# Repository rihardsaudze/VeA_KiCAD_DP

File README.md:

# VeA_KiCAD_R4

**ENG:** This is the main repository for my course work project in PCB design.  
Main objective of this course work is to create an Arduino Uno R3 clone/version, that is adjusted and modified for my own needs.

**LAT:** Šī ir mana projekta galvenā repozitorija, kurā tiks veidots kursa darbs "Datorizētā iespiedplašu projektēšanā"  
Kursa darba laikā plānots izveidot Arduino Uno R3 klonu/versiju, pielāgotu un pārveidotu savām vajadzībām.

***Author/Autors:*** *Rihards*

**Progress:**  
-15.05.2020 pabeigta principiālā shēma (finished schematic)  
-27.05.2020 pabeigts PCB dizains (finished PCB design)  
-09.06.2020 izveidoti GERBER un drill faili (generated GBR and DRL files)

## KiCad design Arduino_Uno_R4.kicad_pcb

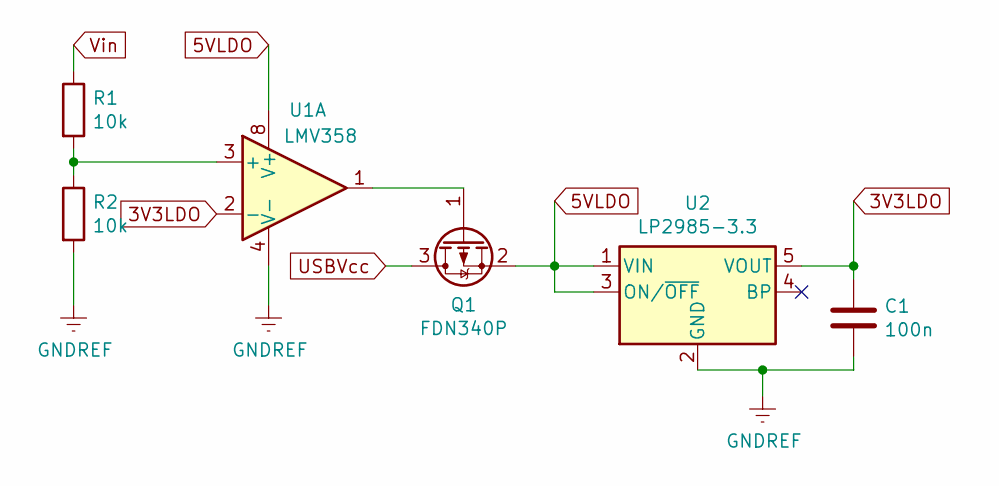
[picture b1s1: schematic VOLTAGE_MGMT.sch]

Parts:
C1: 100n; C_0603_1608Metric
Q1: FDN340P; SOT-23
R1, R2: 10k; R_0603_1608Metric
U1: LMV358; MSOP-8_3x3mm_P0.65mm
U2: LP2985-3.3; SOT-23-5

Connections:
3V3LDO: C1.1, U1.2 (-), U2.5 (VOUT); also elsewhere on the board
5VLDO: Q1.2 (S), U1.8 (V+), U2.1 (VIN), U2.3 (ON/~OFF~); also elsewhere on the board
unnamed: Q1.1 (G), U1.1
unnamed: R1.2, R2.1, U1.3 (+)
USBVcc: Q1.3 (D); also elsewhere on the board
USB_GND: C1.2, R2.2, U1.4 (V-), U2.2 (GND); also elsewhere on the board
Vin: R1.1; also elsewhere on the board

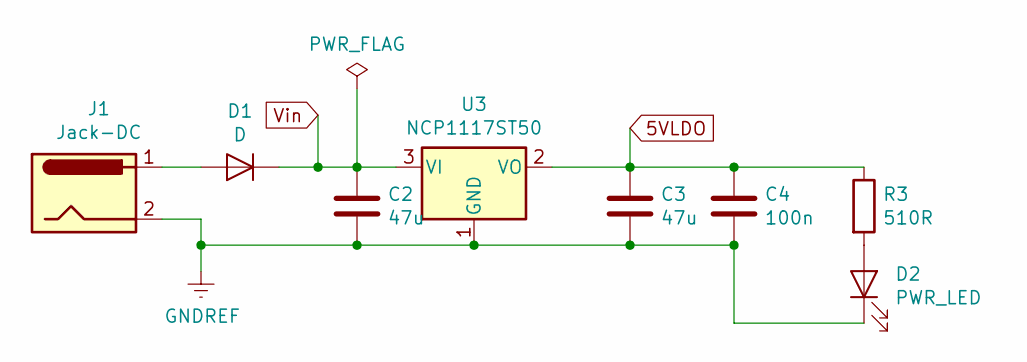
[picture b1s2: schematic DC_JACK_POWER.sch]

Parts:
C2, C3: 47u; C_0805_2012Metric
C4: 100n; C_0603_1608Metric
D1: D; D_SMF
D2: PWR_LED; LED_0603_1608Metric
J1: Jack-DC; DC_Jack
R3: 510R; R_0603_1608Metric
U3: NCP1117ST50; SOT-223-3_TabPin2

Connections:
5VLDO: C3.1, C4.1, R3.1, U3.2 (VO); also elsewhere on the board
unnamed: D1.2 (A), J1.1
unnamed: D2.2 (A), R3.2
USB_GND: C2.2, C3.2, C4.2, D2.1 (K), J1.2, U3.1 (GND); also elsewhere on the board
Vin: C2.1, D1.1 (K), U3.3 (VI); also elsewhere on the board

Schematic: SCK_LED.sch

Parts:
D3: SCK_LED; LED_0603_1608Metric
R4: 510R; R_0603_1608Metric
U1, U4: LMV358; MSOP-8_3x3mm_P0.65mm

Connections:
ICSP_SCK: U1.5 (+); also elsewhere on the board
unnamed: D3.2 (A), R4.2
unnamed: R4.1, U1.6 (-), U1.7
USB_GND: D3.1 (K), U4.4 (V-); also elsewhere on the board

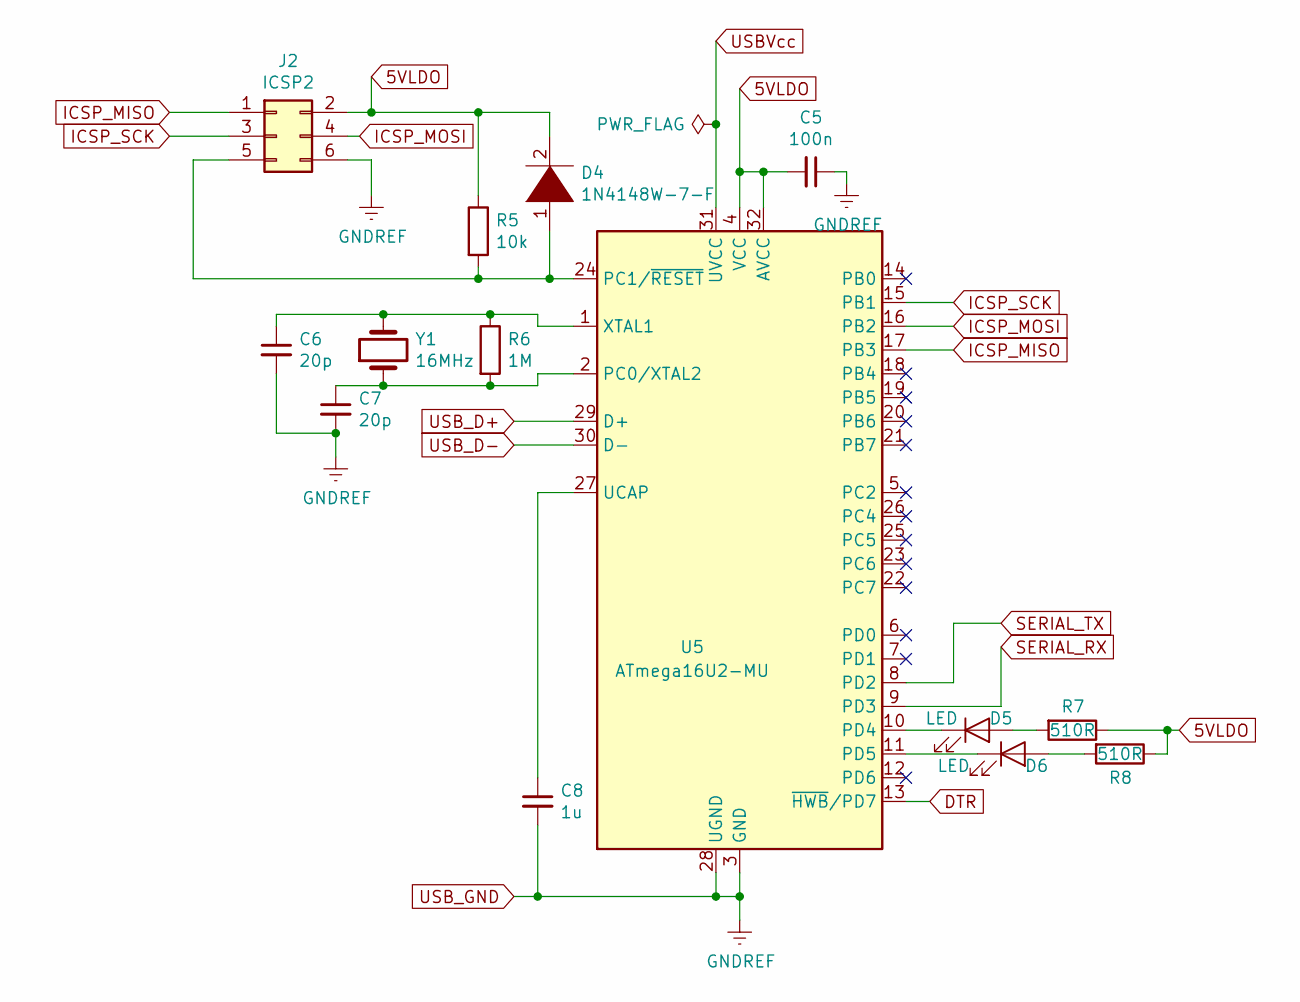
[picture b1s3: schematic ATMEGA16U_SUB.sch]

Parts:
C5: 100n; C_0603_1608Metric
C6, C7: 20p; C_0603_1608Metric
C8: 1u; C_0603_1608Metric
D4: 1N4148W-7-F; D_SOD-123
D5, D6: LED; D_0603_1608Metric
J2: ICSP2; PinHeader_2x03_P2.54mm_Vertical
R5: 10k; R_0603_1608Metric
R6: 1M; R_0603_1608Metric
R7, R8: 510R; R_0603_1608Metric
U5: ATmega16U2-MU; QFN-32-1EP_5x5mm_P0.5mm_EP3.1x3.1mm
Y1: 16MHz; HC-49S

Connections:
5VLDO: C5.2, D4.2 (A), J2.2, R5.1, R7.1, R8.1, U5.4 (VCC), U5.32 (AVCC); also elsewhere on the board
DTR: U5.13 (~HWB~/PD7); also elsewhere on the board
ICSP_MISO: J2.1, U5.17 (PB3)
ICSP_MOSI: J2.4, U5.16 (PB2)
ICSP_SCK: J2.3, U5.15 (PB1); also elsewhere on the board
unnamed: C6.1, R6.1, U5.1 (XTAL1), Y1.2
unnamed: C7.1, R6.2, U5.2 (PC0/XTAL2), Y1.1
unnamed: C8.1, U5.27 (UCAP)
unnamed: D4.1 (K), J2.5, R5.2, U5.24 (PC1/~RESET)
unnamed: D5.1 (K), U5.10 (PD4)
unnamed: D5.2 (A), R7.2
unnamed: D6.1 (K), U5.11 (PD5)
unnamed: D6.2 (A), R8.2
SERIAL_RX: U5.9 (PD3); also elsewhere on the board
SERIAL_TX: U5.8 (PD2); also elsewhere on the board
USBVcc: U5.31 (UVCC); also elsewhere on the board
USB_D+: U5.29 (D+); also elsewhere on the board
USB_D-: U5.30 (D-); also elsewhere on the board
USB_GND: C5.1, C6.2, C7.2, C8.2, J2.6, U5.3 (GND), U5.28 (UGND), U5.33 (GND); also elsewhere on the board

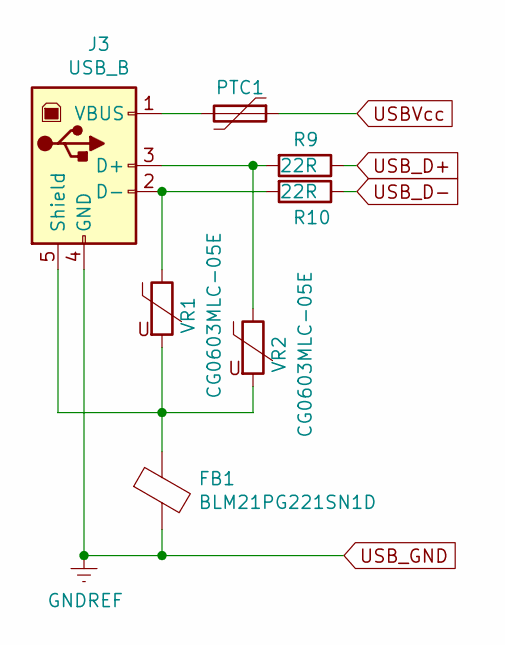
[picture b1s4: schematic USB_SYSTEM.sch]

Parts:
FB1: BLM21PG221SN1D; C_0805_2012Metric
J3: USB_B; USB_B_OST_USB-B1HSxx_Horizontal
PTC1: MF-MSMF-050-2; Fuse_1812_4532Metric
R9, R10: 22R; R_0603_1608Metric
VR1, VR2: CG0603MLC-05E; C_0603_1608Metric

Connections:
unnamed: FB1.1, J3.5 (Shield), VR1.2, VR2.2
unnamed: J3.1 (VBUS), PTC1.2
unnamed: J3.2 (D-), R10.2, VR1.1
unnamed: J3.3 (D+), R9.2, VR2.1
USBVcc: PTC1.1; also elsewhere on the board
USB_D+: R9.1; also elsewhere on the board
USB_D-: R10.1; also elsewhere on the board
USB_GND: FB1.2, J3.4 (GND); also elsewhere on the board

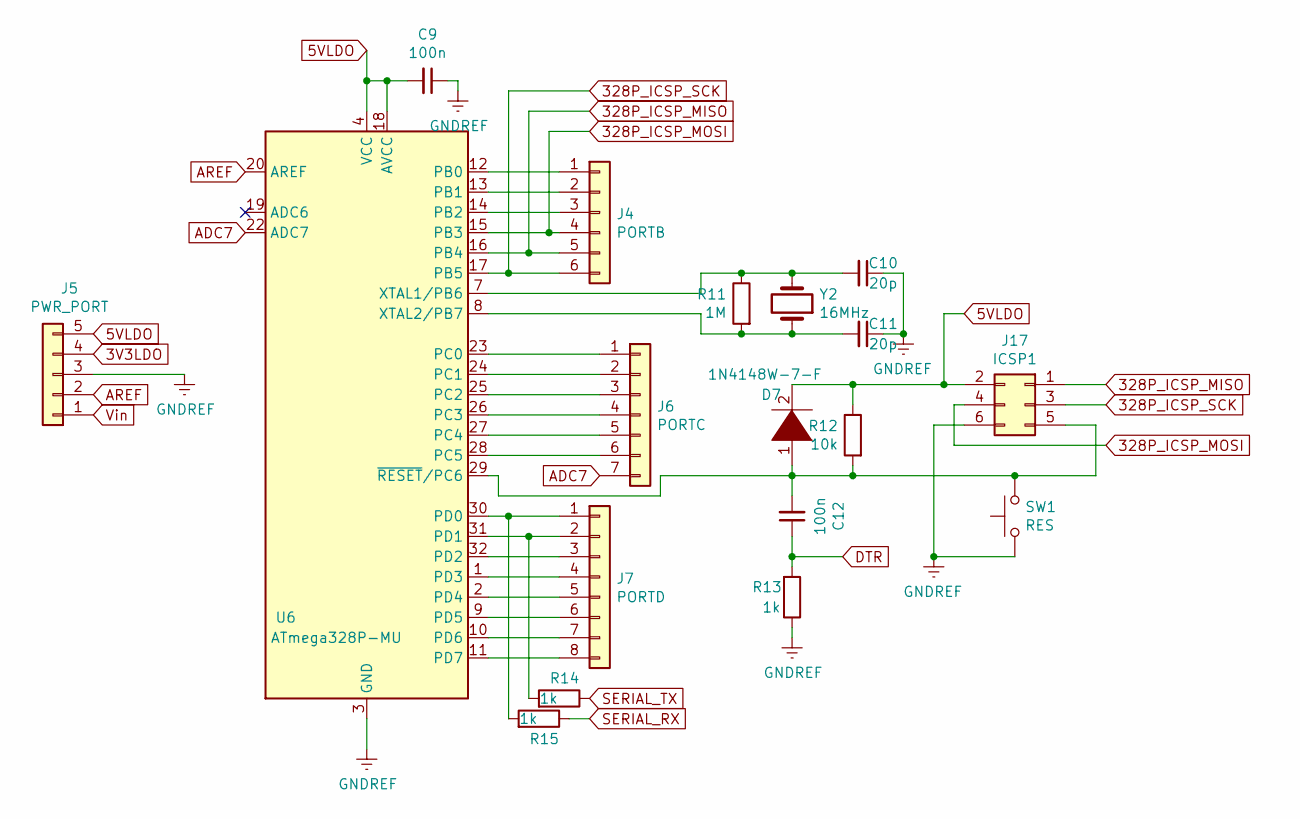
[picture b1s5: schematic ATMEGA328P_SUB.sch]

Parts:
C9, C12: 100n; C_0603_1608Metric
C10, C11: 20p; C_0603_1608Metric
D7: 1N4148W-7-F; D_SOD-123
J4: PORTB; PinHeader_1x06_P2.54mm_Vertical
J5: PWR_PORT; PinHeader_1x05_P2.54mm_Vertical
J6: PORTC; PinHeader_1x07_P2.54mm_Vertical
J7: PORTD; PinHeader_1x08_P2.54mm_Vertical
J17: ICSP1; PinHeader_2x03_P2.54mm_Vertical
R11: 1M; R_0603_1608Metric
R12: 10k; R_0603_1608Metric
R13, R14, R15: 1k; R_0603_1608Metric
SW1: RES; SW_SPST_EVQP2
U6: ATmega328P-MU; QFN-32-1EP_5x5mm_P0.5mm_EP3.1x3.1mm
Y2: 16MHz; HC-49S

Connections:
3V3LDO: J5.4; also elsewhere on the board
5VLDO: C9.2, D7.2 (A), J5.5, J17.2, R12.1, U6.4 (VCC), U6.6 (VCC), U6.18 (AVCC); also elsewhere on the board
328P_ICSP_MISO: J4.5, J17.1, U6.16 (PB4)
328P_ICSP_MOSI: J4.4, J17.4, U6.15 (PB3)
328P_ICSP_SCK: J4.6, J17.3, U6.17 (PB5)
ADC7: J6.7, U6.22 (ADC7)
AREF: J5.2, U6.20 (AREF)
DTR: C12.1, R13.2; also elsewhere on the board
unnamed: C10.2, R11.1, U6.7 (XTAL1/PB6), Y2.2
unnamed: C11.2, R11.2, U6.8 (XTAL2/PB7), Y2.1
unnamed: C12.2, D7.1 (K), J17.5, R12.2, SW1.2, U6.29 (~RESET~/PC6)
unnamed: J4.1, U6.12 (PB0)
unnamed: J4.2, U6.13 (PB1)
unnamed: J4.3, U6.14 (PB2)
unnamed: J6.1, U6.23 (PC0)
unnamed: J6.2, U6.24 (PC1)
unnamed: J6.3, U6.25 (PC2)
unnamed: J6.4, U6.26 (PC3)
unnamed: J6.5, U6.27 (PC4)
unnamed: J6.6, U6.28 (PC5)
unnamed: J7.1, R15.2, U6.30 (PD0)
unnamed: J7.2, R14.2, U6.31 (PD1)
unnamed: J7.3, U6.32 (PD2)
unnamed: J7.4, U6.1 (PD3)
unnamed: J7.5, U6.2 (PD4)
unnamed: J7.6, U6.9 (PD5)
unnamed: J7.7, U6.10 (PD6)
unnamed: J7.8, U6.11 (PD7)
SERIAL_RX: R15.1; also elsewhere on the board
SERIAL_TX: R14.1; also elsewhere on the board
USB_GND: C9.1, C10.1, C11.1, J5.3, J17.6, R13.1, SW1.1, U6.3 (GND), U6.5 (GND), U6.21 (GND), U6.33 (GND); also elsewhere on the board
Vin: J5.1; also elsewhere on the board

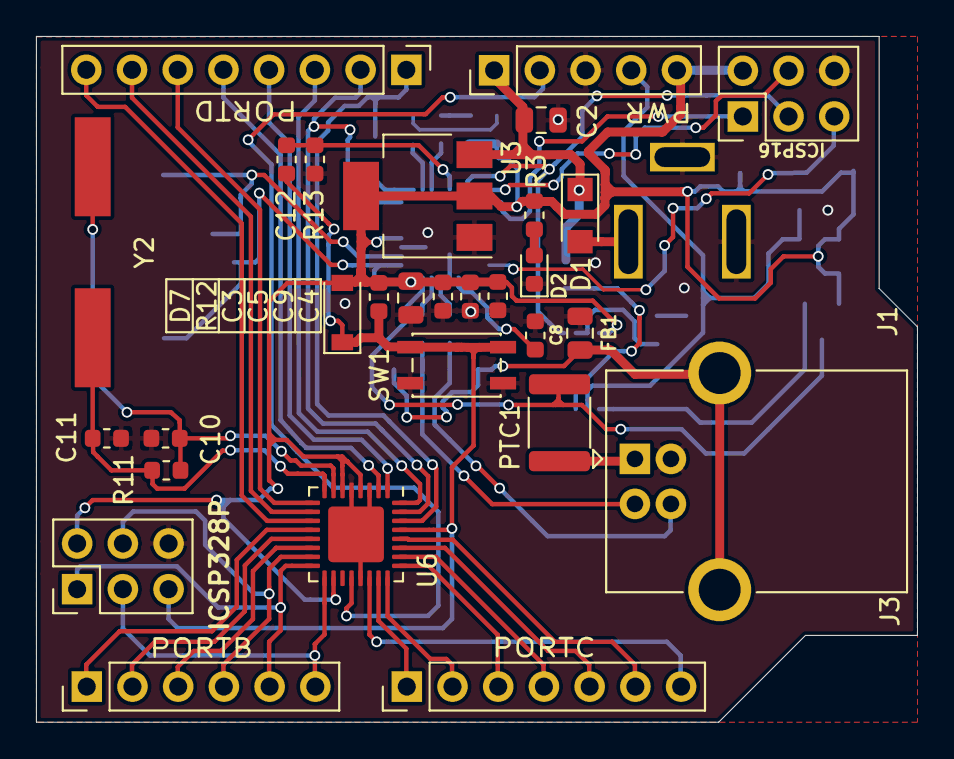
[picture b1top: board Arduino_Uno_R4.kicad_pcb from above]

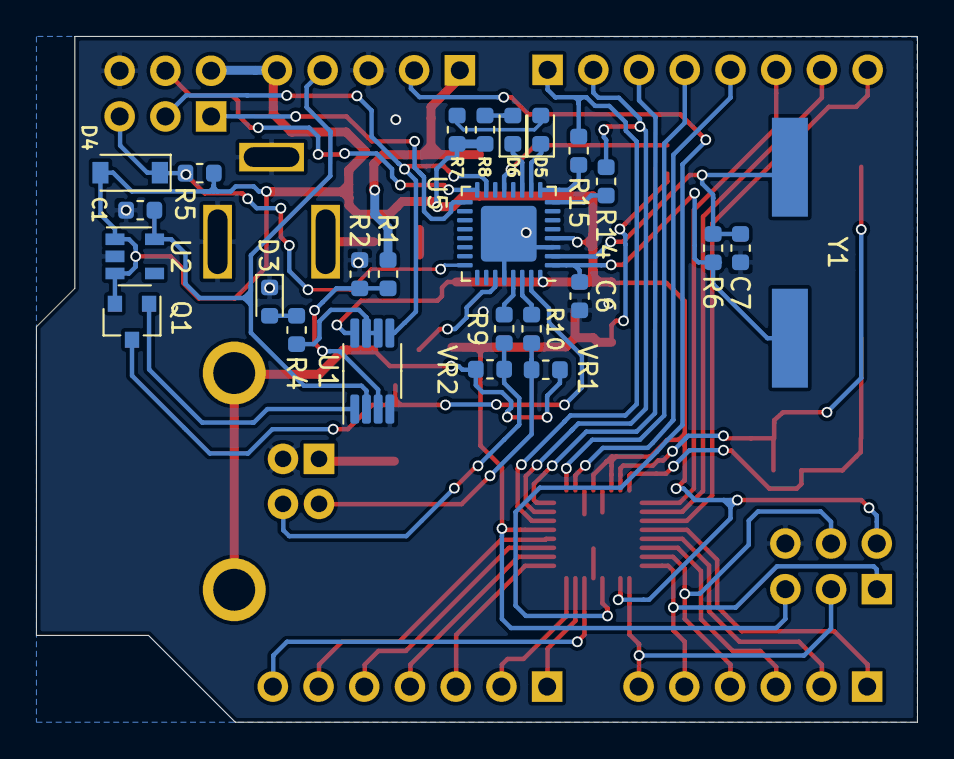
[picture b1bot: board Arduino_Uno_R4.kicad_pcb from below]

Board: 2 copper layers, 48.9 x 38.1 mm, 55 parts (25 on the bottom side), 56 nets.

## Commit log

2020-02-25 Updated README.md file
2020-02-25 Fixed README.md formatting
2020-05-15 Cleaned up and finished schematic
2020-05-20 Set component footprints, added datasheets, fixed the last DRC error and a couple component values
2020-05-24 Updated the schematic, added missing footprints, started PCB design
2020-05-24 Improved readability, fixed component reference positions, added text for IO ports
2020-05-27 Improved consistency of component label positioning, added a couple descriptive labels
2020-06-09 Generated GERBER and drill files
